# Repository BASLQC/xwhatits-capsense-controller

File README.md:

## **IBM Capsense USB Controllers**

[xwhatsit at Geekhack](https://geekhack.org/index.php?topic=58192) has developed a set of USB controllers for the IBM capacitive keyboards (Model F and Beamspring). These allow keyboards that otherwise have no way to hook them up to a modern PC to be used (Beamsprings), offer an alternative to Soarer's excellent converter (standard Model Fs), and also an alternative to the other intriguing capsense project around, the DPH controller. It allows the potential to go a bit further than just a converter if you're trying to do something a bit unusual—like build your own keyboard using old Model F bits, add extra keys that the original controller won't support, or get full make/break scancodes with NKRO on a terminal keyboard.

* The BASLQC has archived the GPLv3 source code [on Github in this repository.](http://github.com/baslqc/xwhatits-capsense-controller) xwhatsit wrote the original controller, we're just forking it within the rights of the GPLv3.
* [Schematics/PCBs/precompiled binaries will available at xwhatsit's website for now.](https://static.wongcornall.com/ibm-capsense-usb/)

### Features

*  Open source! (GPLv3)
*  Approx. 500Hz scan rate with fast debounce
*  **Full NKRO** (without needing to add diodes—yay capacitive keys) over USB on all Windows/Linux/Mac OS X, while retaining boot-mode compatibility for BIOS etc.
*  Auto-calibration of capsense thresholds
*  Media/consumer keys mappable
*  Layer support with 3 function keys; function keys support chording
*  Macro support
*  Cross-platform (Windows/Linux/Mac OS X) graphical configuration utility to set layout/layers/configure scanning
*  Expansion header on all boards to support LEDs, solenoid drivers (for some Beamsprings), buzzers (on Kishsavers) etc.
*  Compact surface-mount design without needing to plug in external Teensys etc.

## The Controllers

### Beamspring-USB-Rev4
[attach=1]
This supports the standard Beamspring boards, such as the 5251, 3278, 3727 etc., which have a 23x4 matrix. It **will not** work on a Beamspring Displaywriter despite the identical 30-pin connector, as these have a 12x8 matrix—see below for that controller.

This can be paired with the solenoid driver board (see below) for Extra Loud Click, if your Beamspring is fitted with a solenoid (the 3727 is the only one I'm aware of that isn't).

USB connects via an on-board mini-USB socket.

PCB at OSHPark: http://oshpark.com/shared_projects/bOXMsRYH

### Beamspring-Displaywriter-USB-Rev1
[attach=2]
This is to support the unusual Beamspring Displaywriter keyboards, which have a very different 12x8 matrix, with interleaved rows. They will not work with a Model F Displaywriter; as far as I'm aware these have built-in (non-removable) controllers.

USB connects via an on-board mini-USB socket.

PCB at OSHPark: http://oshpark.com/shared_projects/KcxYPs3y

### Model-F-USB-Rev1
[attach=3]

(photo shows Rev1 boards)
Rev2 PCB below (black lines show the actual board cutout):
[img width=640 height=145]http://uploads.oshpark.com/uploads/project/top_image/eTR858GJ/i.png[/img]

This should work with all Model F keyboards (including the Kishsaver) which have separate controllers. Unfortunately this excludes the XT and a couple of other terminal boards, which have a controller-on-board which can't be removed (except maybe with a hacksaw).

Some Model F keyboards have less than 16 columns; columns can be set to `skip' using the GUI util.

These do unfortunately require soldering; IBM used a soldered-on ribbon cable for the Model F controllers, that first needs to be removed from the old controller, then attached to this one.

In the Rev2 board (unlike the Rev1 in the photo below, which has a flying lead), a USB micro (not mini!) is socket is used. This is to reduce board size a bit and these days USB micro sockets are much more common.

PCB at OSHPark: http://oshpark.com/shared_projects/eTR858GJ

## Accessory boards

### Beamspring-USB-Solenoid-Driver-Rev2
[attach=4]
(photo shows prototype, not Rev2)

This is drive the solenoid fitted to most beamspring keyboads. It runs off the USB voltage supply to the main controller, and uses a current-limited switch-mode power supply to boost up to 9V. This is then used to fire the solenoid when a key is pressed for Extra Loud Click coupled with Small Blinking Light.

PCB at OSHPark: http://oshpark.com/shared_projects/qdZwUHLH

### Model-F-3178-Adaptor-Rev1
[img width=640 height=33]http://uploads.oshpark.com/uploads/project/top_image/bD4fQlCX/i.png[/img]
[img width=640 height=33]http://uploads.oshpark.com/uploads/project/bottom_image/bD4fQlCX/i.png[/img]

An adaptor board for IBM 3178 keyboards, which were kind of an unusual Model F version of a 3278/3727 Beamspring. They unfortunately have a different pinout and require this adaptor.

PCB at OSHPark: http://oshpark.com/shared_projects/bD4fQlCX

## GUI Util
[attach=5]
This is a Qt application which runs on Linux, Windows and Mac OS X. Its main purpose is to allow you to set which key location corresponds to which scancode:
[attach=6]
...but also allows tweaking expansion port settings, like whether to run in LED mode for Caps/Num/Scroll Lock indicators, or whether to fire a solenoid (and adjust timings of it etc.).

This also is handy for diagnostic output to show which keys are being sensed as up or down.

## Building your own
Give it a go! Sourcecode/schematics/PCB layouts are here: http://downloads.cornall.co/ibm-capsense-usb . You can order pre-Gerbered PCBs from OSHPark by using the links above, or checking my profile on OSHPark here: http://oshpark.com/profiles/xwhatsit . There are people around (me included) who will help you if you run into issues. Surface-mount is easier than through-hole, it just looks scary!

## Pricing/Availability
As mentioned above, these are open-source. If you have a soldering iron and flux, consider building your own! Don't be put off the surface mount soldering, several people (some with no previous surface-mount experience) have now built their own.

However if you're not into picking up resistors with tweezers, I can build one for you and pre-program and test it first. For this, check out the group buy thread over here: http://geekhack.org/index.php?topic=58192

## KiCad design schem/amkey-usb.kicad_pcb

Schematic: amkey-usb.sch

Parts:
C1, C2: 22pF
C3: 4.7uF
C4, C6, C7, C8, C9, C10, C11, C12: 0.1uF
C5: 1uF
P1: USB
P2: CONN_3X2
P3: Columns
P4: Rows
R1, R2: 22
R3, R6: 20K
R4, R7: 4.7K
R5, R9: 10K
R8: 1K
RP1, RP2: 10K
RP3, RP4: 100K
SW1: PROG
SW2: RESET
U1: ATMEGA32U2
U2: DAC101S101; MODULE
U3, U4: LM339A
U5, U6: 74AHC595
X1: 16MHz

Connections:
/SPI_MOSI: U1.16, U2.4 (DIN)
/SPI_SCLK: U1.15, U2.5 (SCLK)
/SPI_SS: U1.14, U2.6 (SYNC)
/USB_D+: P1.3 (D+), R2.1
/USB_D-: P1.2 (D-), R1.1
/USB_SHIELD: C6.1, P1.6 (SHELL1)
Col1: P3.1, U5.15 (QA)
Col2: P3.3, U5.1 (QB)
Col3: P3.5, U5.2 (QC)
Col4: P3.7, U5.3 (QD)
Col5: P3.9, U5.4 (QE)
Col6: P3.11, U5.5 (QF)
Col7: P3.13, U5.6 (QG)
Col8: P3.15, U5.7 (QH)
Col9: P3.17, U6.15 (QA)
Col10: P3.19, U6.1 (QB)
Col11: P3.21, U6.2 (QC)
Col12: P3.23, U6.3 (QD)
Col13: P3.25, U6.4 (QE)
Col14: P3.27, U6.5 (QF)
Col15: P3.29, U6.6 (QG)
Col16: P3.31, U6.7 (QH)
GND: C1.1, C2.1, C3.2, C4.1, C5.2, C6.2, C7.2, C8.2, C9.1, C10.1, C11.2, C12.2, P1.5 (GND), P2.6, P3.2, P3.4, P3.6, P3.8, P3.10, P3.12, P3.14, P3.16, P3.18, P3.20, P3.22, P3.24, P3.26, P3.28, P3.30, P3.32, P4.2, P4.4, P4.6, P4.8, P4.10, P4.12, P4.14, P4.16, R4.2, R8.2, SW1.1, SW2.2, U1.3, U1.28, U2.2 (GND), U3.12 (GND), U4.12 (GND), U5.8 (GND), U6.8 (GND); also elsewhere on the board
unnamed: R2.2, U1.29
unnamed: R1.2, U1.30
unnamed: C5.1, U1.27
unnamed: C2.2, U1.1, X1.2
unnamed: R3.1, R4.1, R6.2, U3.4 (-), U3.6 (-), U3.8 (-), U3.10 (-), U4.4 (-), U4.6 (-), U4.8 (-), U4.10 (-)
unnamed: C8.1, R5.2, SW2.1, U1.24
unnamed: P2.4, U1.20
unnamed: P2.5, U1.19
unnamed: P2.3, U1.18
unnamed: P2.2, U1.21
unnamed: U5.9 (~QH), U6.14 (SER)
unnamed: R6.1, U2.1 (VOUT)
unnamed: R7.2, R8.1, RP3.1, RP3.2, RP3.3, RP3.4, RP4.1, RP4.2, RP4.3, RP4.4
unnamed: C1.2, U1.2, X1.1
Row1: P4.1, RP3.5 (R4), U3.11 (+)
Row2: P4.3, RP3.6 (R3), U3.9 (+)
Row3: P4.5, RP3.7 (R2), U3.7 (+)
Row4: P4.7, RP3.8 (R1), U3.5 (+)
Row5: P4.9, RP4.5 (R4), U4.11 (+)
Row6: P4.11, RP4.6 (R3), U4.9 (+)
Row7: P4.13, RP4.7 (R2), U4.7 (+)
Row8: P4.15, RP4.8 (R1), U4.5 (+)
RowOP1: RP1.4, U1.26, U3.13
RowOP2: RP1.3, U1.25, U3.14
RowOP3: RP1.2, U1.23, U3.1
RowOP4: RP1.1, U1.22, U3.2
RowOP5: RP2.4, U1.6, U4.13
RowOP6: RP2.3, U1.7, U4.14
RowOP7: RP2.2, U1.8, U4.1
RowOP8: RP2.1, U1.9, U4.2
SR_DS: U1.10, U5.14 (SER)
SR_OE: U1.11, U5.13 (G), U6.13 (G)
SR_SHCP: R9.2, SW1.2, U1.13, U5.11 (SRCLK), U6.11 (SRCLK)
SR_STCP: U1.12, U5.12 (RCLK), U6.12 (RCLK)
VCC: C3.1, C4.2, C7.1, C9.2, C10.2, C11.1, C12.1, P1.1 (VBUS), P2.1, R3.2, R5.1, R7.1, R9.1, RP1.5 (R4), RP1.6 (R3), RP1.7 (R2), RP1.8 (R1), RP2.5 (R4), RP2.6 (R3), RP2.7 (R2), RP2.8 (R1), U1.4, U1.31, U1.32, U2.3 (VA), U3.3 (V+), U4.3 (V+), U5.10 (SRCLR), U5.16 (VCC), U6.10 (SRCLR), U6.16 (VCC)

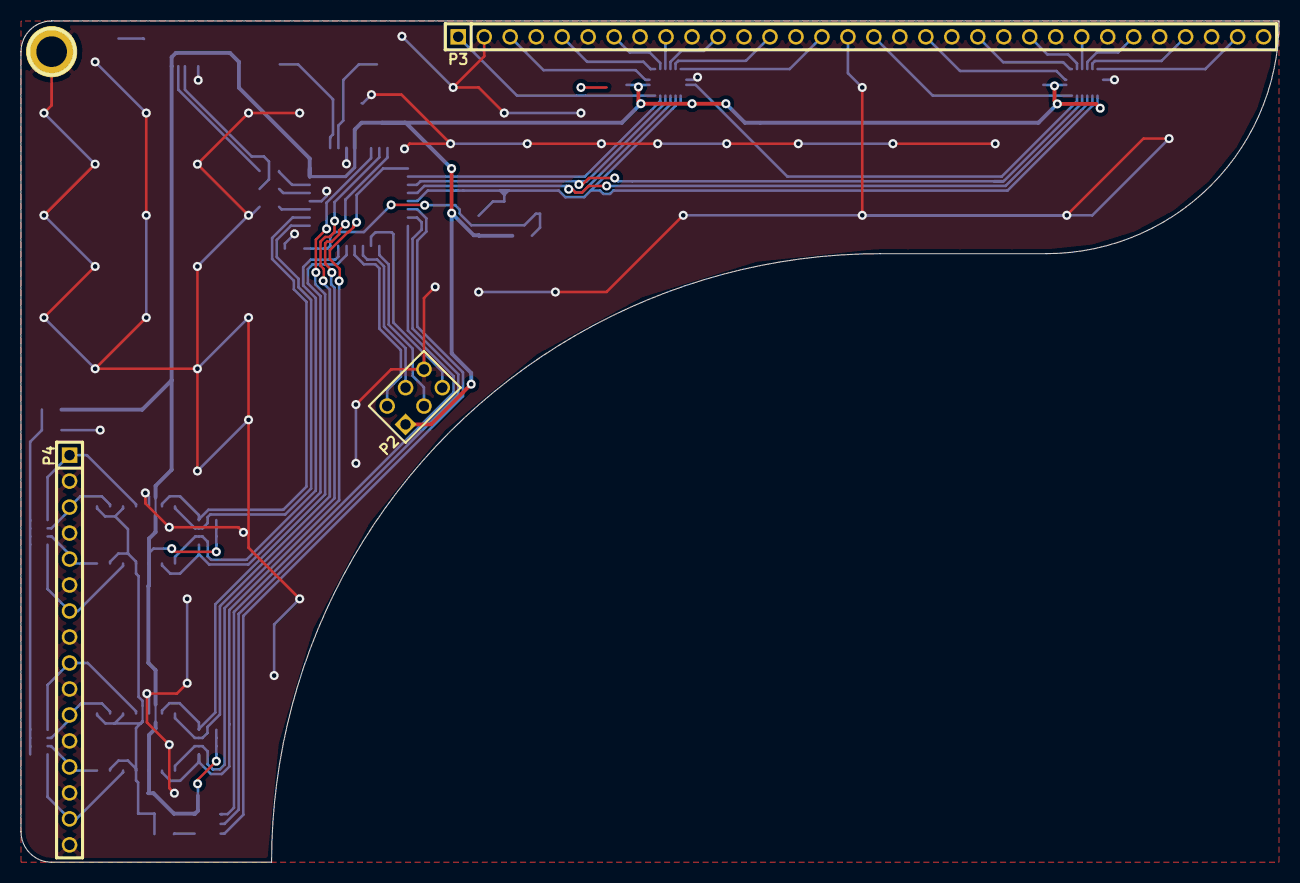
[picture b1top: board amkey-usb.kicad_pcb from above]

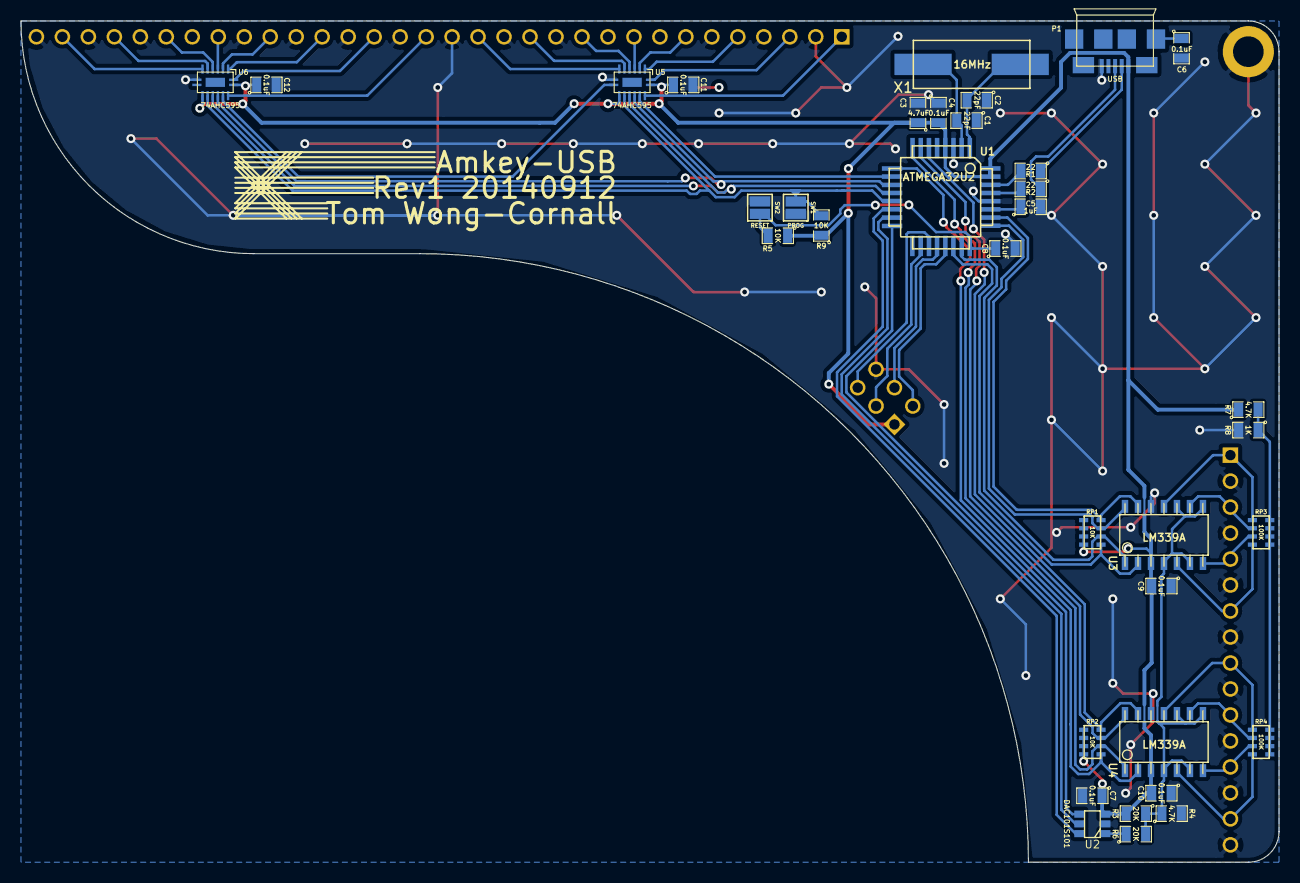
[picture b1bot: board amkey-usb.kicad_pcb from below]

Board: 2 copper layers, 123.0 x 82.2 mm, 39 parts (35 on the bottom side), 58 nets.

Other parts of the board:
1PIN: P***; 1pin

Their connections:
GND: 1PIN.1; also elsewhere on the board

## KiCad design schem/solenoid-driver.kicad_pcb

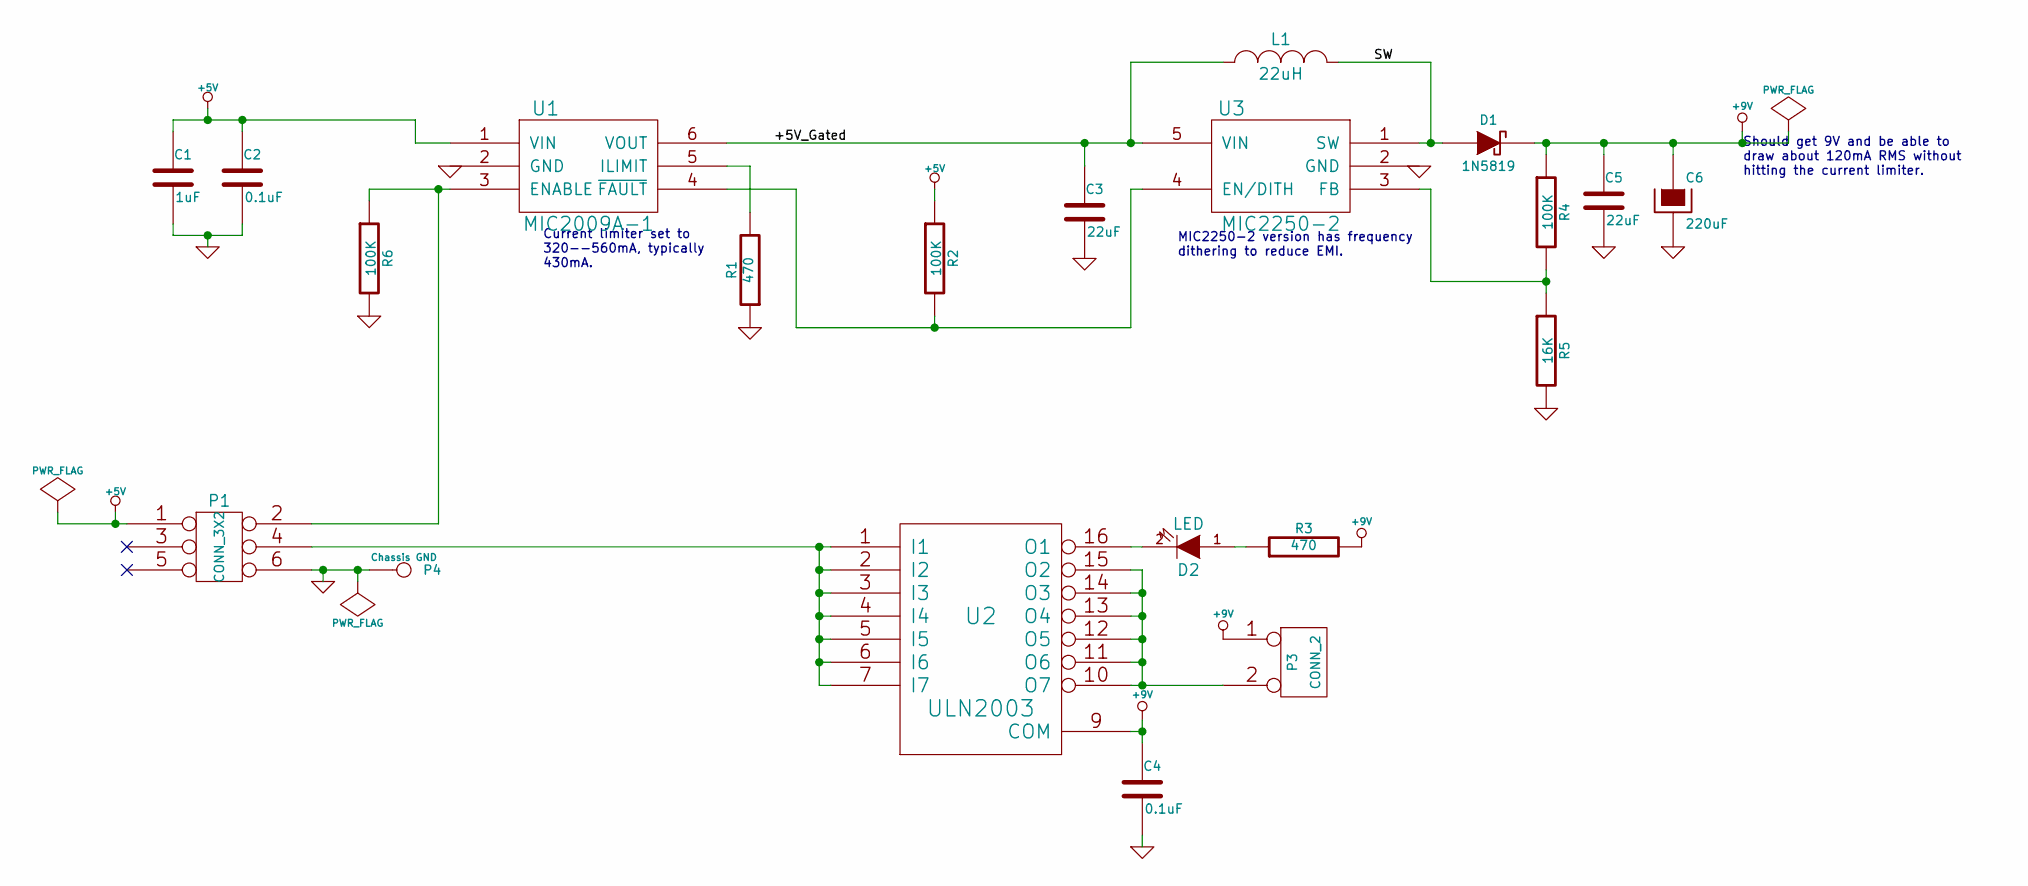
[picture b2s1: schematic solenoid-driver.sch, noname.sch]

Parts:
C1: 1uF
C2, C4: 0.1uF
C3, C5: 22uF
C6: 220uF
D1: 1N5819
D2: LED
L1: 22uH
P1: CONN_3X2
P3: CONN_2
P4: Chassis GND
R1, R3: 470
R2, R4, R6: 100K
R5: 16K
U1: MIC2009A-1
U2: ULN2003
U3: MIC2250-2

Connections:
+5V: C1.1, C2.1, P1.1, R2.1, U1.1 (VIN)
+9V: C4.1, C5.1, C6.1, D1.2 (K), P3.1, R3.2, R4.1, U2.9 (COM)
/+5V_Gated: C3.1, L1.1, U1.6 (VOUT), U3.5 (VIN)
/SW: D1.1 (A), L1.2, U3.1 (SW)
GND: C1.2, C2.2, C3.2, C4.2, C5.2, C6.2, P1.6, P4.1, R1.1, R5.2, R6.2, U1.2 (GND), U2.8 (GND), U3.2 (GND)
unnamed: R1.2, U1.5 (ILIMIT)
unnamed: P1.4, U2.1 (I1), U2.2 (I2), U2.3 (I3), U2.4 (I4), U2.5 (I5), U2.6 (I6), U2.7 (I7)
unnamed: P3.2 (PM), U2.10 (O7), U2.11 (O6), U2.12 (O5), U2.13 (O4), U2.14 (O3), U2.15 (O2)
unnamed: P1.2, R6.1, U1.3 (ENABLE)
unnamed: D2.2 (K), U2.16 (O1)
unnamed: D2.1 (A), R3.1
unnamed: R2.2, U1.4 (~FAULT), U3.4 (EN/DITH)
unnamed: R4.2, R5.1, U3.3 (FB)

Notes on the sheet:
Should get 9V and be able to draw about 120mA RMS without hitting the current limiter.
Current limiter set to 320--560mA, typically 430mA.
MIC2250-2 version has frequency dithering to reduce EMI.

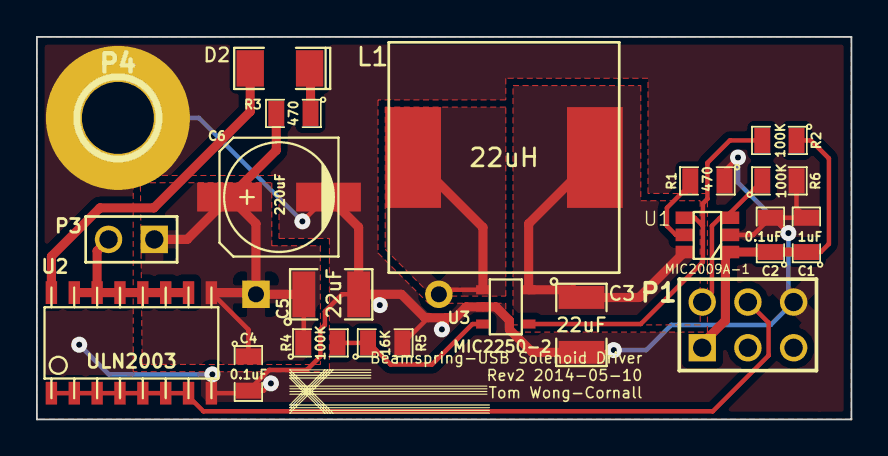
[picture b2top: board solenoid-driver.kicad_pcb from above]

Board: 2 copper layers, 45.2 x 21.2 mm, 21 parts (1 on the bottom side), 13 nets.

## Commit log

2015-09-11 initial commit, 0.6.1
2015-09-11 0.6.2
2015-09-11 0.6.6
2015-09-11 0.6.7, imported from xwhatit's untracked source code
2015-09-11 0.7.0, imported from xwhatits untracked repository
2015-09-11 0.7.1, imported from xwhatits untracked repository
2015-09-11 0.8.0, imported from xwhatits untracked repository
2015-09-11 0.9.0, imported from xwhatits untracked repository
2015-09-11 Add GPLv3 per author's wishes
2015-09-11 Create README.md based on original forum post
    https://geekhack.org/index.php?topic=58138.0
